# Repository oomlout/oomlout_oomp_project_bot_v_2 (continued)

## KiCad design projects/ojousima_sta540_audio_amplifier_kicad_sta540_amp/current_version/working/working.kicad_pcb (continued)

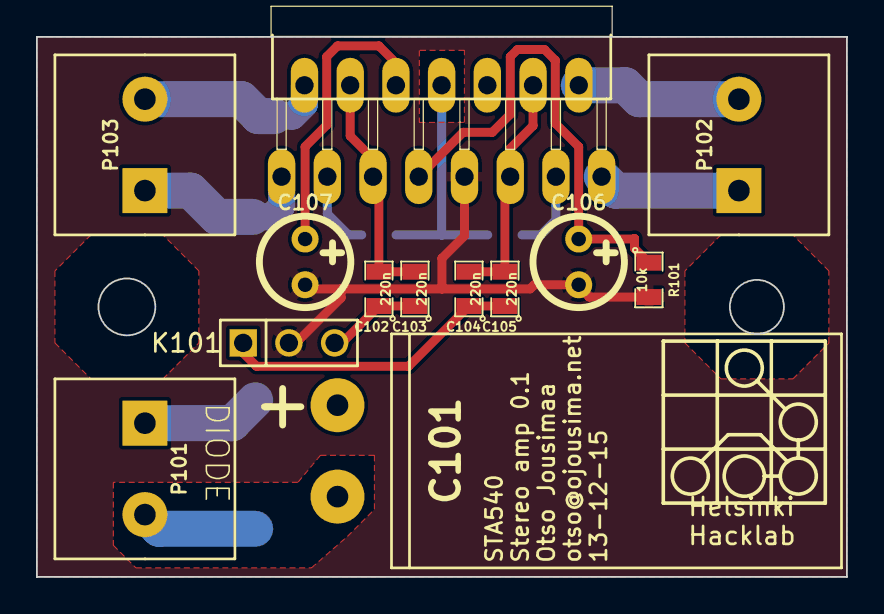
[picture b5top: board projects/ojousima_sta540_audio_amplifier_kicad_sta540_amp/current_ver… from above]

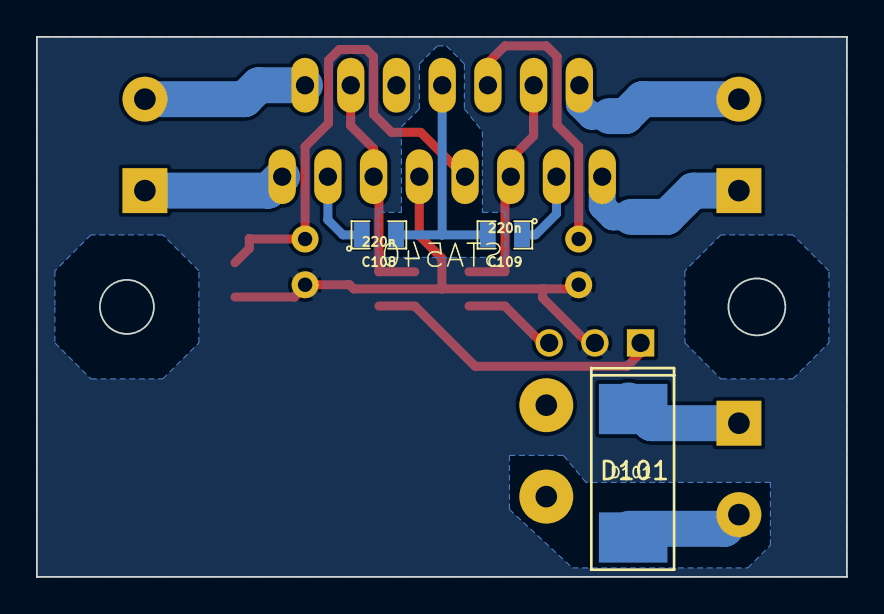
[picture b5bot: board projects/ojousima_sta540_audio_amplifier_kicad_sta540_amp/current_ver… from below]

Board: 4 copper layers, 45.0 x 30.0 mm, 16 parts (3 on the bottom side), 12 nets.

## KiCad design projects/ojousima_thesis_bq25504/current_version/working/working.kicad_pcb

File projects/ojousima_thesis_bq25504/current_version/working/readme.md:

# thesis
 
## summary 
* id: ojousima_thesis_bq25504
* user: ojousima
* name: thesis
* board: bq25504
* repo: https://github.com/ojousima/thesis
* src_file_repo_kicad_pcb: hardware/BQ25504/bq25504.kicad_pcb
* src_file_repo_kicad_pcb_link: https://github.com/ojousima/thesis/tree/master/hardware/BQ25504/bq25504.kicad_pcb

* src_file_repo_sch: hardware/BQ25504/bq25504.sch
* src_file_repo_sch_link: https://github.com/ojousima/thesis/tree/master/hardware/BQ25504/bq25504.sch
* full details link: https://github.com/oomlout/oomlout_oomp_project_bot_v_2/tree/main/projects/ojousima_thesis_bq25504/current_version/working

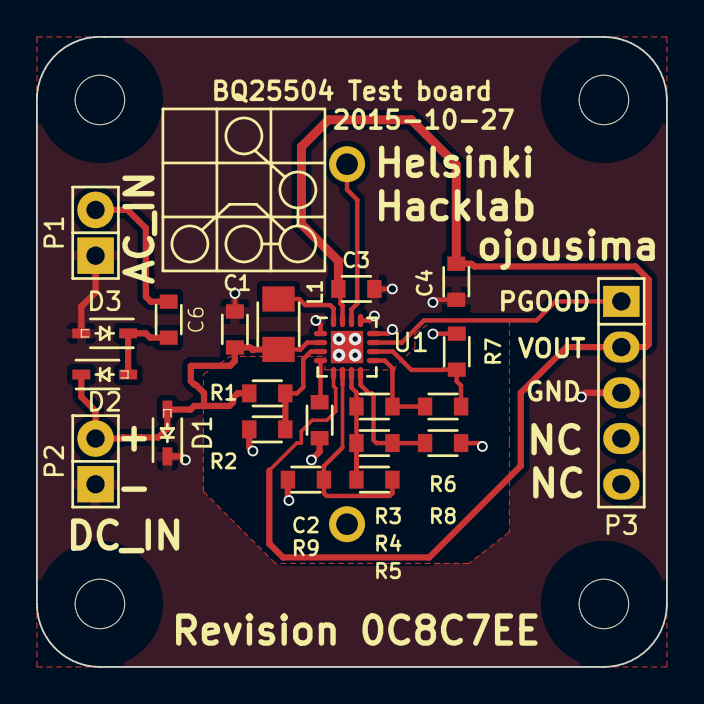
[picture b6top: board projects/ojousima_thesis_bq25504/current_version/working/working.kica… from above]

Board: 2 copper layers, 35.0 x 35.0 mm, 27 parts (1 on the bottom side), 15 nets.

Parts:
C1, C2, C3, C4, C6: C; SMD0603_A
C5: EECRG0V155(V|H)N; EECRG0V155HN
D1: TVS; SOD-323-A
D2, D3: D_Schottky; SOD-323-A
L1: INDUCTOR_SMALL; SMD1206_A
NC1, NC2, NC3, NC4: Mounting_hole; m2.5_mechanical_npth_mount
P1, P2: CONN_01X02; Pin_Header_Straight_1x02
P3: CONN_01X03; Pin_Header_Straight_1x05
R1, R2, R3, R4, R5, R6, R7, R8, R9: R_Small; SMD0603_A
U1: BQ25504; QFN-16-1EP_3x3mm_Pitch0.5mm

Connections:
/HYST: R3.2, R6.1, U1.9
/PROG: R6.2, R7.1, U1.10
/VBAT_OK: P3.1, U1.11
/VBOV: R5.2, R9.1, U1.6
/VBUV: R4.2, R8.1, U1.8
/V_IN: C1.1, D1.2, D2.1, L1.1, P2.2, R1.1, U1.2
/V_OC_SAMP: R1.2, R2.1, U1.3
/V_RDIV: R3.1, R4.1, R5.1, U1.7
/V_REF: C2.2, U1.4
/V_SYS: C3.1, C4.1, P3.2, U1.5, U1.15
GND: C1.2, C2.1, C3.2, C4.2, C5.2, D1.1, D3.2, P1.1, P2.1, P3.3, R2.2, R7.2, R8.2, R9.2, U1.1, U1.12, U1.13, U1.17
unnamed: C5.1, U1.14
unnamed: C6.1, D2.2, D3.1
unnamed: C6.2, P1.2
unnamed: L1.2, U1.16

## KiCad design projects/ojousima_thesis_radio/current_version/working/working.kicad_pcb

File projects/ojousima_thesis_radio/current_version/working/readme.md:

# thesis
 
## summary 
* id: ojousima_thesis_radio
* user: ojousima
* name: thesis
* board: radio
* repo: https://github.com/ojousima/thesis
* src_file_repo_kicad_pcb: hardware/radio/radio.kicad_pcb
* src_file_repo_kicad_pcb_link: https://github.com/ojousima/thesis/tree/master/hardware/radio/radio.kicad_pcb

* src_file_repo_sch: hardware/BQ25504/bq25504.sch
* src_file_repo_sch_link: https://github.com/ojousima/thesis/tree/master/hardware/BQ25504/bq25504.sch
* full details link: https://github.com/oomlout/oomlout_oomp_project_bot_v_2/tree/main/projects/ojousima_thesis_radio/current_version/working

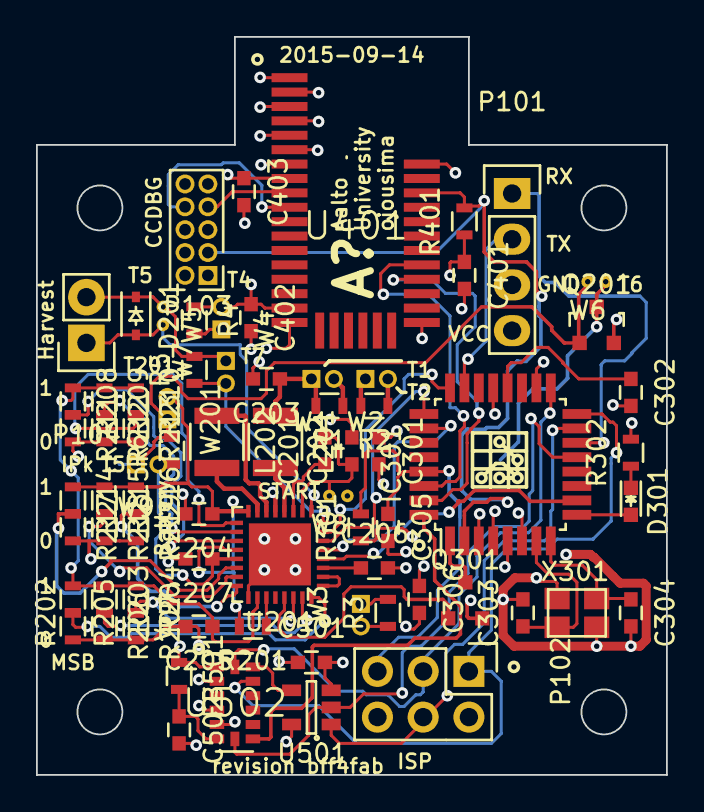
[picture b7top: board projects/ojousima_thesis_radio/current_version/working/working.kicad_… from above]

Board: 4 copper layers, 35.0 x 41.0 mm, 74 parts (1 on the bottom side), 57 nets.

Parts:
BT201: Battery; CR2032-holder-S8421R
C201: 1µ; C_0603
C202, C203, C204, C207, C306: C; C_0603
C205, C301, C302, C305, C501, C502: 100n; C_0603
C206: 4u7; C_0603
C303, C304: 22p; C_0603
C401, C402, C403: 470n; C_0603
D201: TVS; SOD-323
D301: LED; LED-0603
FB501: FILTER; R_0603
IC301: ATMEGA328-A; TQFP-32_7x7mm_Pitch0.8mm
L201, L202: INDUCTOR; R_1210
P101: CONN_01X04; Pin_Header_Straight_1x04
P102: CONN_02X03; Pin_Header_Straight_2x03
P103: CONN_02X05; Pin_Header_Straight_2x05_Pitch1.27mm
P104: CONN_01X02; Pin_Header_Straight_1x02
Q201, Q301: BSH105; SOT-23
R1, R2, R3, R4, R5, R6, R201, R202, R203, R204, R205, R206, R207, R208, R209, R210, R211, R212, R213, R214, R215, R216, R217, R218, R219, R302: R; R_0603
R301, R401: 10k; R_0603
U201: LTC3331; QFN-32-1EP_5x5mm_Pitch0.5mm
U401: BLE113
U501: SN74AUP1T32; SOT-23-5
U502: ADXL375; LGA-14_(CC-14-1)
W1, W2, W3, W4, W7, W9, W201: TEST; Test_pair_TH_small
W5, W6, W8: TEST; Test_pair_TH_tiny
X301: 8MHz; crystal_FA238-TSX3225

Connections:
/Bluetooth/P2_1-PROG: P103.8, U401.10
/Bluetooth/P2_2-PROG: P103.7, U401.9
/Bluetooth/RXD: IC301.31, U401.28
/Bluetooth/VCC_BLE: C401.1, C402.1, C403.1, P103.1, P103.10, R4.1, R401.1, U401.8, U401.17, W4.2
/Control/BLE_RS: IC301.2, P103.3, R401.2, U401.34
/Control/EH_ON: Q301.1, U201.29
/Control/INT0: IC301.32, U502.8
/Control/INT1: IC301.1, Q301.3
/Control/MISO: IC301.16, P102.1, U502.12
/Control/MOSI: IC301.15, P102.4, U501.1
/Control/RESET: C305.1, IC301.29, P102.5, R301.2
/Control/RX: IC301.30, U401.29
/Control/SCK: IC301.17, P102.3, U502.14
/Control/SW_RX: IC301.14, P101.1
/Control/SW_TX: IC301.23, P101.2
/Control/UV0: IC301.24, U201.7
/Control/UV1: IC301.25, U201.6
/Control/UV2: IC301.26, U201.5
/Control/UV3: IC301.10, U201.4
/Control/VCC_uc: C301.1, C306.1, IC301.4, IC301.6, IC301.18, P101.4, P102.2, R2.1, R301.1, W2.2
/Power management/BB_IN: C204.1, R201.2, R214.1, R215.1, R216.1, U201.16, U201.20, W201.2
/Power management/FLOAT0: R216.2, R219.1, U201.24
/Power management/FLOAT1: R215.2, R218.1, U201.23
/Power management/Harvest1: D201.1, P104.2, R5.2, W5.2, W7.1
/Power management/Harvest2: D201.2, P104.1, U201.9, W5.1
/Power management/IPK0: R210.2, R213.1, U201.17
/Power management/IPK1: R209.2, R212.1, U201.18
/Power management/IPK2: R208.2, R211.1, U201.19
/Power management/LBSEL: R214.2, R217.1, U201.22
/Power management/OUT0: R204.2, R207.1, U201.30
/Power management/OUT1: R203.2, R206.1, U201.31
/Power management/OUT2: R202.2, R205.1, U201.32
/Power management/VIN2: C206.1, U201.3
/Power management/VIN3: C205.1, R202.1, R203.1, R204.1, R208.1, R209.1, R210.1, U201.26
/Power management/VOUT: C203.1, L201.1, R1.2, U201.13, W1.1
/Sensor/CS: IC301.13, U501.2, U502.7
/Sensor/VCC_ACC: C501.1, FB501.1, R3.1, U501.5, U502.1, W3.2
GND: C202.2, C203.2, C204.2, C205.2, C206.2, C207.2, C301.2, C302.2, C303.2, C304.2, C305.2, C306.2, C401.2, C402.2, C403.2, C501.2, C502.2, IC301.3, IC301.5, IC301.21, P101.3, P102.6, P103.9, Q201.2, Q301.2, R205.2, R206.2, R207.2, R211.2, R212.2, R213.2, R217.2, R218.2, R219.2, R302.2, U201.25, U201.33, U401.1, U401.2, U401.3, U401.4, U401.5, U401.6, U401.7, U401.18, U401.25, U401.36, U501.3, U502.2, U502.4, U502.5, W8.2, X301.3
unnamed: BT201.1, Q201.1, R6.2, W6.1, W9.1, W201.1
unnamed: BT201.2, Q201.3, W6.2
unnamed: C201.1, U201.11
unnamed: C201.2, C202.1, U201.10, W8.1
unnamed: C207.1, R6.1, U201.21, W9.2
unnamed: C302.1, IC301.20
unnamed: C303.1, IC301.7, X301.1
unnamed: C304.1, IC301.8, X301.2
unnamed: C502.1, FB501.2, U502.6
unnamed: D301.1, R302.1
unnamed: D301.2, IC301.9
unnamed: L201.2, U201.12
unnamed: L202.1, U201.14
unnamed: L202.2, U201.15
unnamed: R5.1, U201.8, W7.2
unnamed: R201.1, U201.27
unnamed: U201.1, U201.2
unnamed: U501.4, U502.13
VCC: R1.1, R2.2, R3.2, R4.2, W1.2, W2.1, W3.1, W4.1
